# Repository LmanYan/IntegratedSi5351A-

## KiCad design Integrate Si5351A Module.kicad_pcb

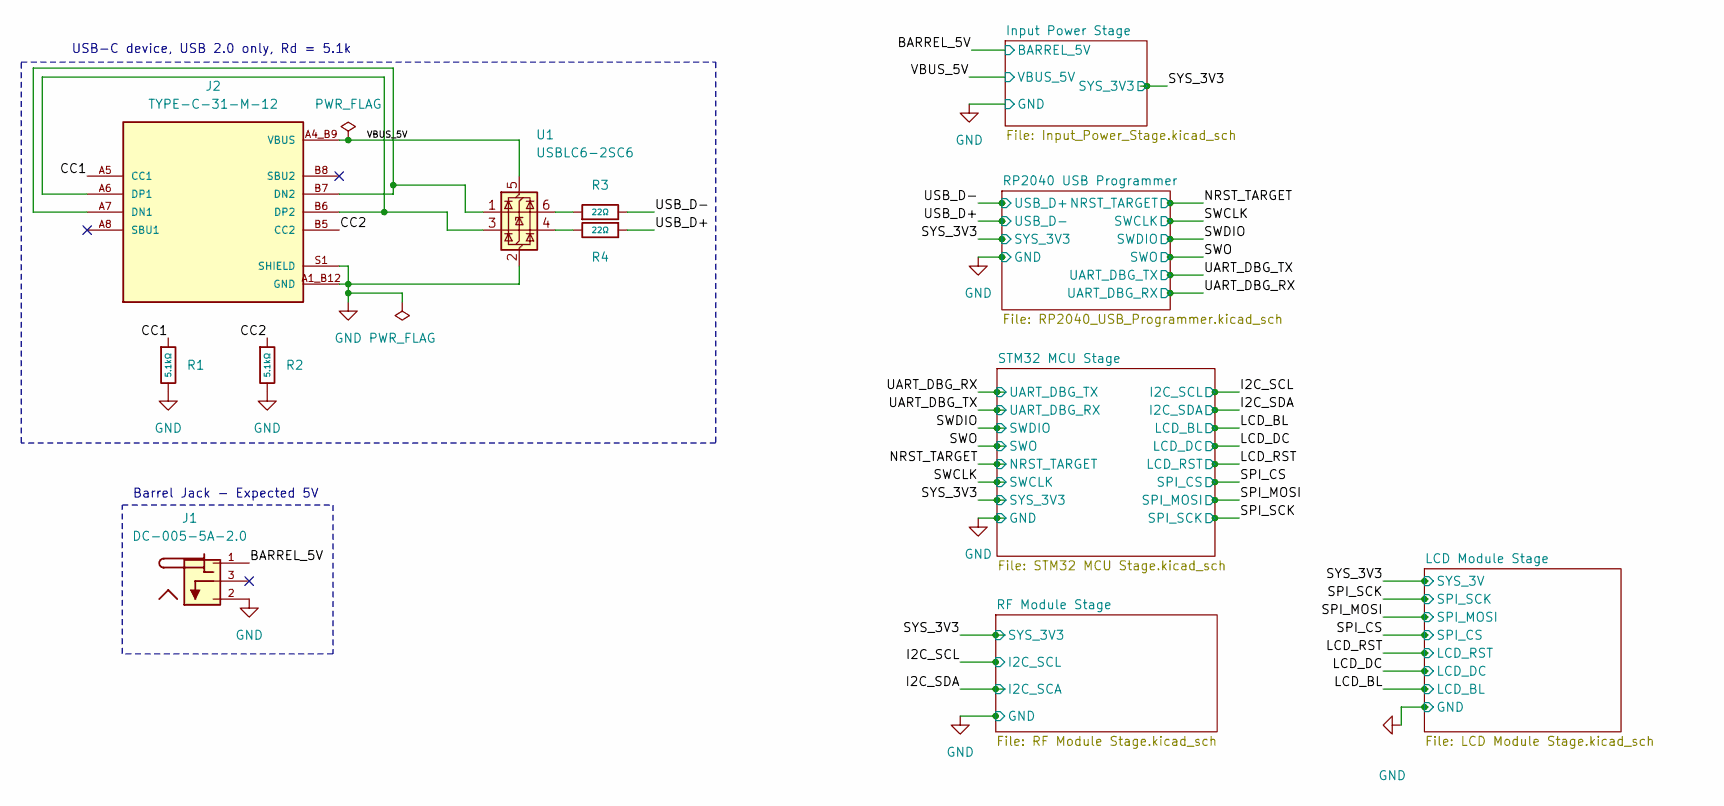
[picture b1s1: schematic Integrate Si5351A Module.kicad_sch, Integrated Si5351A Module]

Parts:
J1: DC-005-5A-2.0; XKB_DC-005-5A-2.0; PARTREV A0
J2: TYPE-C-31-M-12; HRO_TYPE-C-31-M-12; PARTREV 2020.12.08
R1, R2: 5.1kΩ; R_0603; Overload Voltage (Max) 75V; Tolerance ±1%; Part 0603WAF5101T5E; LCSC C23186
R3, R4: 22Ω; R_0603; Overload Voltage (Max) 75V; Tolerance ±1%; Part 0603WAF220JT5E; LCSC C23345
U1: USBLC6-2SC6; SOT-23-6

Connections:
/BARREL_5V: J1.1; also elsewhere on the board
/CC1: J2.A5 (CC1), R1.1
/CC2: J2.B5 (CC2), R2.1
/USB_D+: R4.1; also elsewhere on the board
/USB_D-: R3.2; also elsewhere on the board
GND: J1.2, J2.A1_B12 (GND), J2.B1_A12 (GND), J2.S1 (SHIELD), J2.S2 (SHIELD), J2.S3 (SHIELD), J2.S4 (SHIELD), R1.2, R2.2, U1.2 (GND); also elsewhere on the board
unnamed: J2.A7 (DN1), J2.B7 (DN2), U1.1 (I/O1)
unnamed: J2.A6 (DP1), J2.B6 (DP2), U1.3 (I/O2)
unnamed: R3.1, U1.6 (I/O1)
unnamed: R4.2, U1.4 (I/O2)
VBUS: J2.A4_B9 (VBUS), J2.B4_A9 (VBUS), U1.5 (VBUS); also elsewhere on the board

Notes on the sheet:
USB-C device, USB 2.0 only, Rd = 5.1k
Barrel Jack - Expected 5V

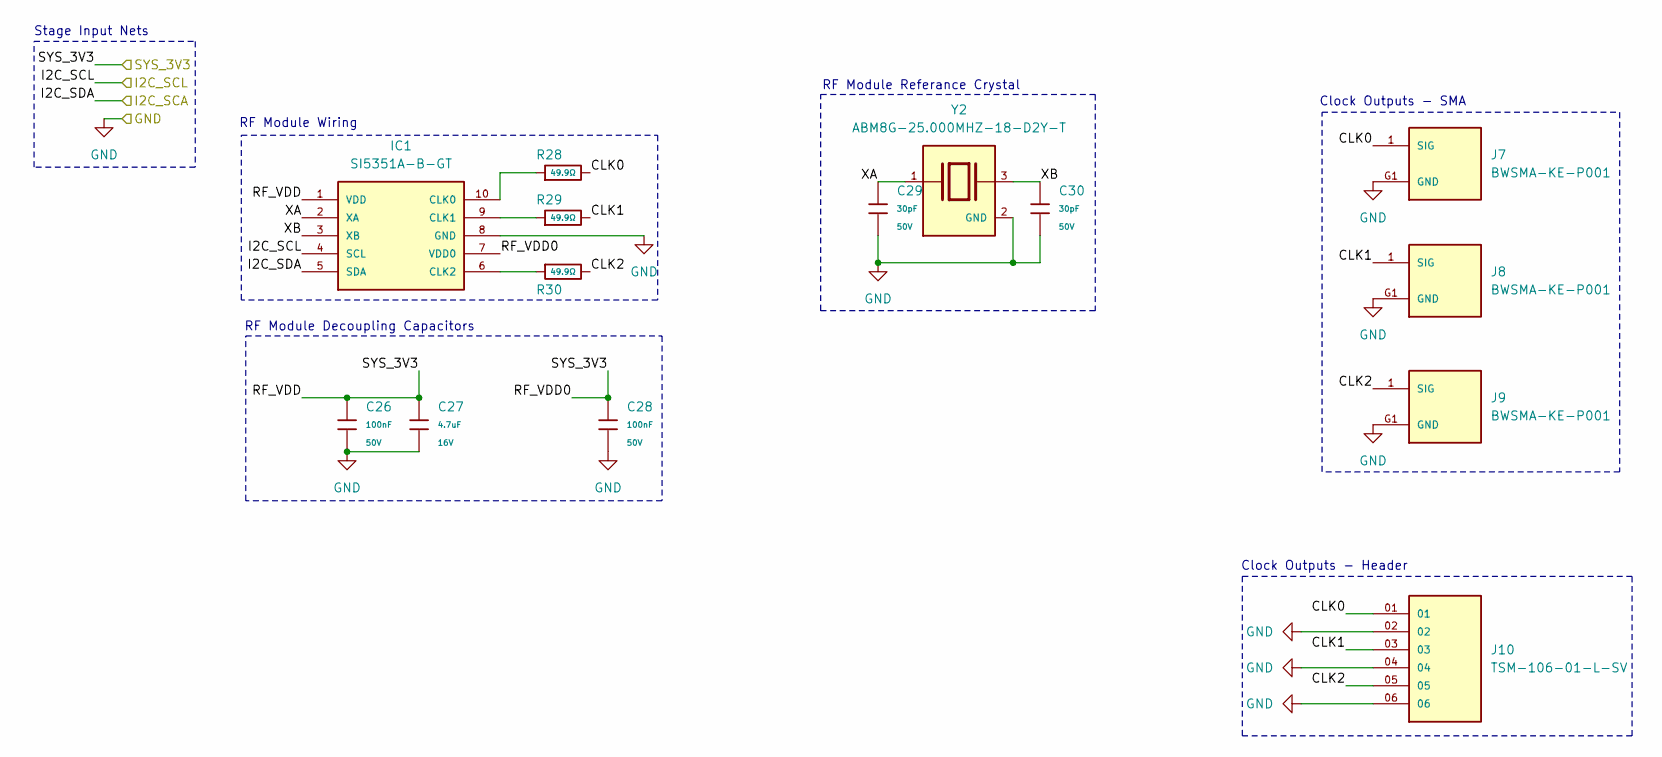
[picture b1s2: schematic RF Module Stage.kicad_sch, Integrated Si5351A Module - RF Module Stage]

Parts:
C26, C28: 100nF; C_0603; Voltage Rated 50V; Tolerance ±10%; Part CC0603KRX7R9BB104; LCSC C14663
C27: 4.7uF; C_0603; Voltage Rated 16V; Tolerance ±10%; Part CL10A475KO8NNNC; LCSC C19666
C29, C30: 30pF; C_0603; Voltage Rated 50V; Tolerance ±5%; Part 0603CG300J500NT; LCSC C1658
IC1: SI5351A-B-GT; SOP50P490X110-10N; MOUSER_PART_NUMBER 634-SI5351A-B-GT
J7, J8, J9: BWSMA-KE-P001; BATWIRELESS_BWSMA-KE-P001; PARTREV A
J10: TSM-106-01-L-SV; SAMTEC_TSM-106-01-L-SV
R28, R29, R30: 49.9Ω; R_0603; Overload Voltage (Max) 75V; Tolerance ±1%; Part 0603WAF499JT5E; LCSC C23185
Y2: ABM8G-25.000MHZ-18-D2Y-T; XTAL_ABM8G-25.000MHZ-18-D2Y-T; PARTREV 08.13.15

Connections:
/I2C_SCL: IC1.4 (SCL); also elsewhere on the board
/I2C_SDA: IC1.5 (SDA); also elsewhere on the board
/RF Module Stage/CLK0: J7.1 (SIG), J10.01, R28.2
/RF Module Stage/CLK1: J8.1 (SIG), J10.03, R29.2
/RF Module Stage/CLK2: J9.1 (SIG), J10.05, R30.2
/RF Module Stage/XA: C29.1, IC1.2 (XA), Y2.1
/RF Module Stage/XB: C30.1, IC1.3 (XB), Y2.3
/SYS_3V3: C26.1, C27.1, C28.1, IC1.1 (VDD), IC1.7 (VDD0); also elsewhere on the board
GND: C26.2, C27.2, C28.2, C29.2, C30.2, IC1.8 (GND), J7.G1 (GND), J7.G2 (GND), J7.G3 (GND), J7.G4 (GND), J8.G1 (GND), J8.G2 (GND), J8.G3 (GND), J8.G4 (GND), J9.G1 (GND), J9.G2 (GND), J9.G3 (GND), J9.G4 (GND), J10.02, J10.04, J10.06, Y2.2 (GND), Y2.4 (GND); also elsewhere on the board
unnamed: IC1.10 (CLK0), R28.1
unnamed: IC1.9 (CLK1), R29.1
unnamed: IC1.6 (CLK2), R30.1

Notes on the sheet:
RF Module Referance Crystal
RF Module Decoupling Capacitors
Clock Outputs - Header
RF Module Wiring
Stage Input Nets
Clock Outputs - SMA

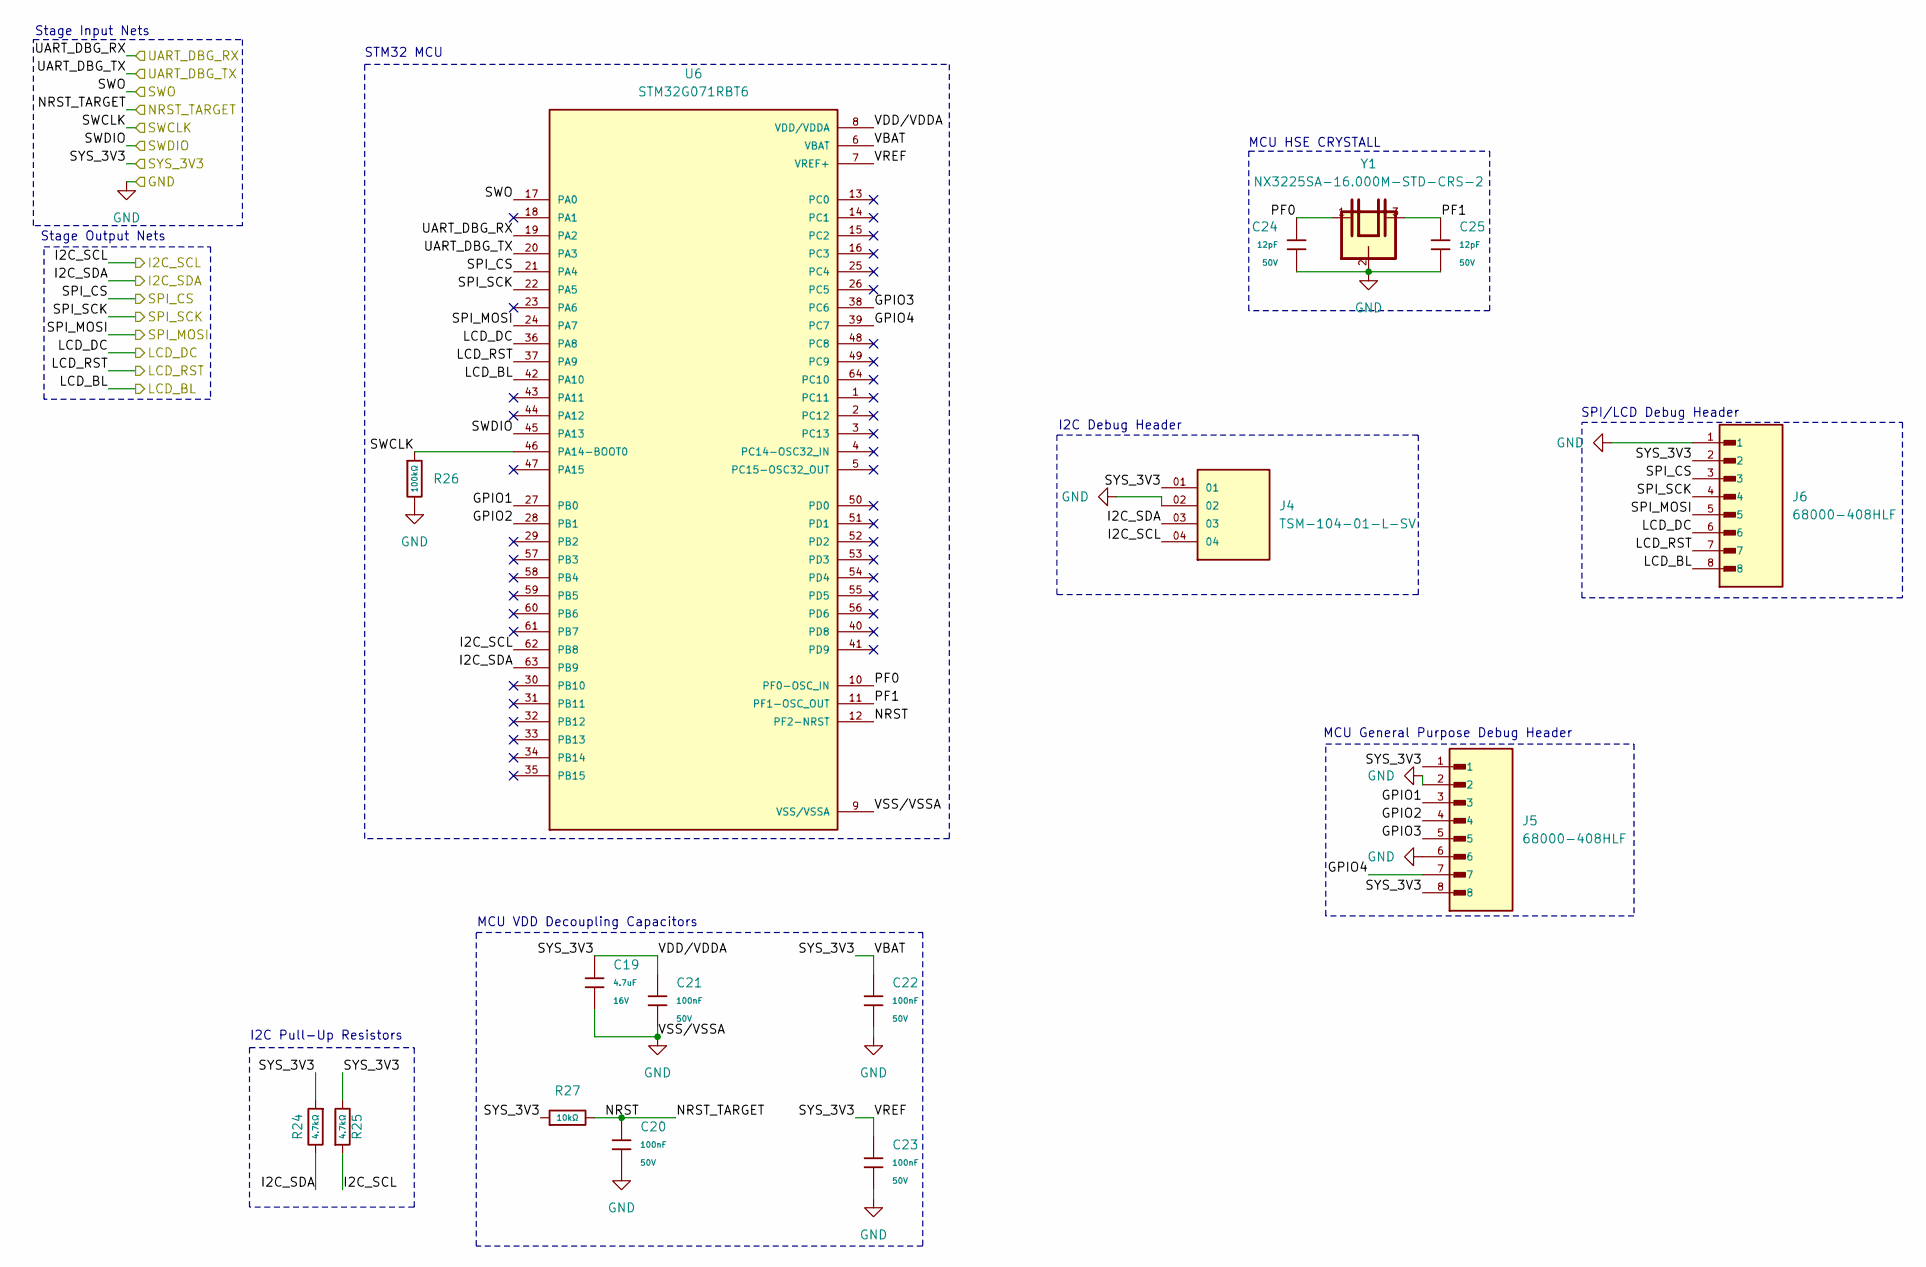
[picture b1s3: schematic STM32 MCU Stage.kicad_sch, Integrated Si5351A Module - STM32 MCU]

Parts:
C19: 4.7uF; C_0603; Voltage Rated 16V; Tolerance ±10%; Part CL10A475KO8NNNC; LCSC C19666
C20, C21, C22, C23: 100nF; C_0603; Voltage Rated 50V; Tolerance ±10%; Part CC0603KRX7R9BB104; LCSC C14663
C24, C25: 12pF; C_0603; Voltage Rated 50V; Tolerance ±5%; Part CL10C120JB8NNNC; LCSC C38523
J4: TSM-104-01-L-SV; SAMTEC_TSM-104-01-L-SV
J5, J6: 68000-408HLF; AMPHENOL_68000-408HLF; PARTREV DG
R24, R25: 4.7kΩ; R_0603; Overload Voltage (Max) 75V; Tolerance ±1%; Part 0603WAF4701T5E; LCSC C23162
R26: 100kΩ; R_0603; Overload Voltage (Max) 75V; Tolerance ±1%; Part 0603WAF1003T5E; LCSC C25803
R27: 10kΩ; R_0603; Overload Voltage (Max) 75V; Tolerance ±1%; Part 0603WAF1002T5E; LCSC C25804
U6: STM32G071RBT6; QFP50P1200X1200X160-64N; PARTREV 2
Y1: NX3225SA-16.000M-STD-CRS-2; OSCCC320X250X60N

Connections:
/I2C_SCL: J4.04, R25.1, U6.62 (PB8); also elsewhere on the board
/I2C_SDA: J4.03, R24.2, U6.63 (PB9); also elsewhere on the board
/LCD_BL: J6.8, U6.42 (PA10); also elsewhere on the board
/LCD_DC: J6.6, U6.36 (PA8); also elsewhere on the board
/LCD_RST: J6.7, U6.37 (PA9); also elsewhere on the board
/NRST_TARGET: C20.1, R27.2, U6.12 (PF2-NRST); also elsewhere on the board
/SPI_CS: J6.3, U6.21 (PA4); also elsewhere on the board
/SPI_MOSI: J6.5, U6.24 (PA7); also elsewhere on the board
/SPI_SCK: J6.4, U6.22 (PA5); also elsewhere on the board
/STM32 MCU Stage/GPIO1: J5.3, U6.27 (PB0)
/STM32 MCU Stage/GPIO2: J5.4, U6.28 (PB1)
/STM32 MCU Stage/GPIO3: J5.5, U6.38 (PC6)
/STM32 MCU Stage/GPIO4: J5.7, U6.39 (PC7)
/STM32 MCU Stage/PF0: C24.1, U6.10 (PF0-OSC_IN), Y1.1
/STM32 MCU Stage/PF1: C25.1, U6.11 (PF1-OSC_OUT), Y1.3
/SWCLK: R26.1, U6.46 (PA14-BOOT0); also elsewhere on the board
/SWDIO: U6.45 (PA13); also elsewhere on the board
/SWO: U6.17 (PA0); also elsewhere on the board
/SYS_3V3: C19.1, C21.1, C22.1, C23.1, J4.01, J5.1, J5.8, J6.2, R24.1, R25.2, R27.1, U6.6 (VBAT), U6.7 (VREF+), U6.8 (VDD/VDDA); also elsewhere on the board
/UART_DBG_RX: U6.20 (PA3); also elsewhere on the board
/UART_DBG_TX: U6.19 (PA2); also elsewhere on the board
GND: C19.2, C20.2, C21.2, C22.2, C23.2, C24.2, C25.2, J4.02, J5.2, J5.6, J6.1, R26.2, U6.9 (VSS/VSSA), Y1.2, Y1.4; also elsewhere on the board

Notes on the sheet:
STM32 MCU
SPI/LCD Debug Header
Stage Input Nets
I2C Pull-Up Resistors
MCU General Purpose Debug Header
MCU VDD Decoupling Capacitors
Stage Output Nets
I2C Debug Header
MCU HSE CRYSTALL

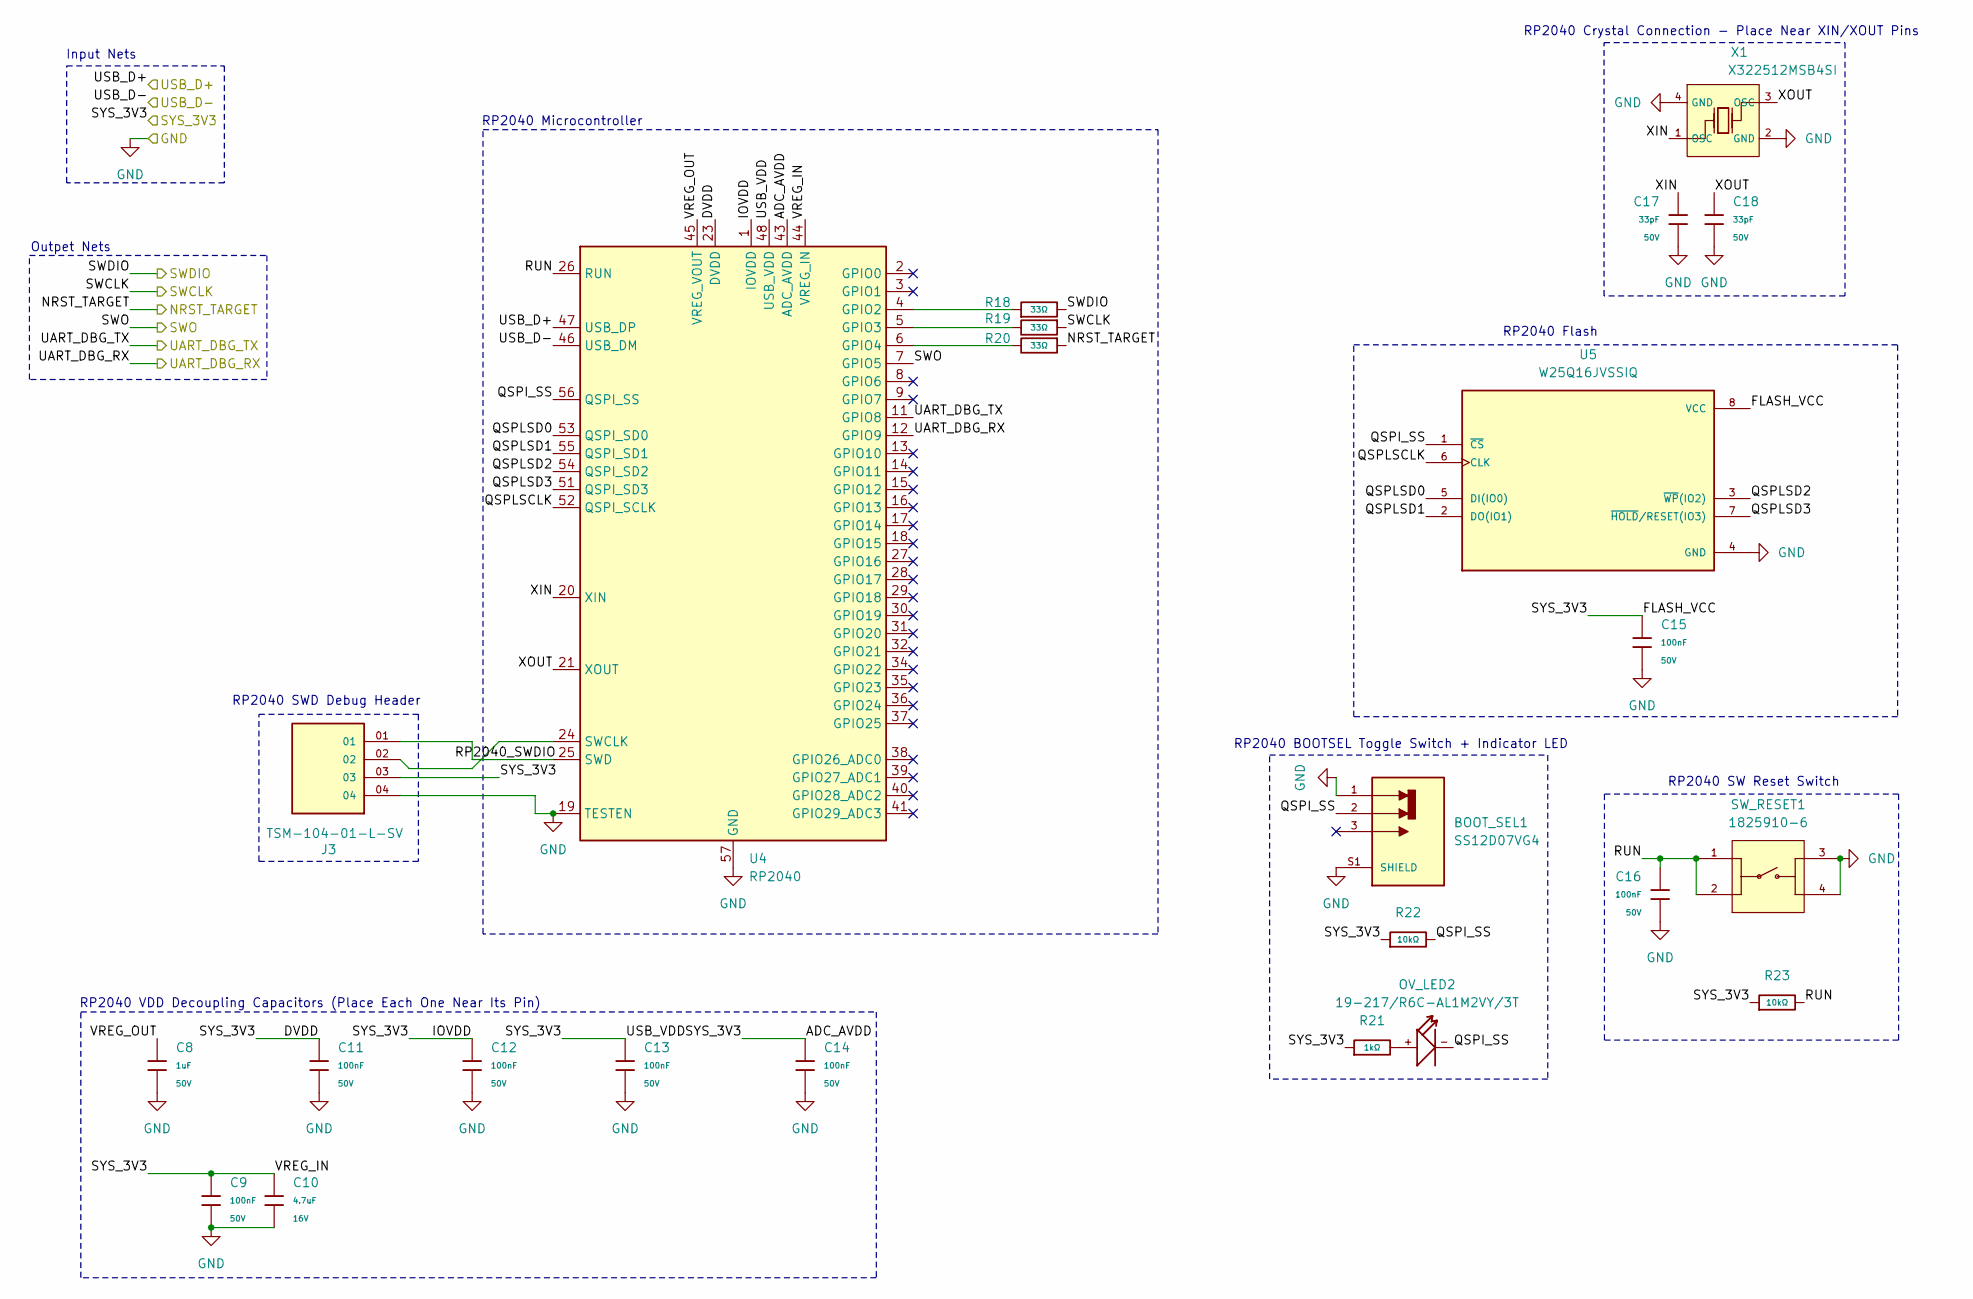
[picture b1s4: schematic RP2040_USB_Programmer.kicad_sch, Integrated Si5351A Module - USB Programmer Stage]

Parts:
BOOT_SEL1: SS12D07VG4; SW_SS12D07VG4; PARTREV 1
C8: 1uF; C_0603; Voltage Rated 50V; Tolerance ±10%; Part CL10A105KB8NNNC; LCSC C15849
C9, C11, C12, C13, C14, C15, C16: 100nF; C_0603; Voltage Rated 50V; Tolerance ±10%; Part CC0603KRX7R9BB104; LCSC C14663
C10: 4.7uF; C_0603; Voltage Rated 16V; Tolerance ±10%; Part CL10A475KO8NNNC; LCSC C19666
C17, C18: 33pF; C_0603; Voltage Rated 50V; Tolerance ±5%; Part CL10C330JB8NNNC; LCSC C1663
J3: TSM-104-01-L-SV; SAMTEC_TSM-104-01-L-SV
OV_LED2: 19-217/R6C-AL1M2VY/3T; LED-0603; MPN 19-217-R6C-AL1M2VY-3T
R18, R19, R20: 33Ω; R_0603; Overload Voltage (Max) 75V; Tolerance ±1%; Part 0603WAF330JT5E; LCSC C23140
R21: 1kΩ; R_0603; Overload Voltage (Max) 75V; Tolerance ±1%; Part 0603WAF1001T5E; LCSC C21190
R22, R23: 10kΩ; R_0603; Overload Voltage (Max) 75V; Tolerance ±1%; Part 0603WAF1002T5E; LCSC C25804
SW_RESET1: 1825910-6; SW_1825910-6-4; PARTREV C10
U4: RP2040; QFN-56-1EP_7x7mm_P0.4mm_EP3.2x3.2mm_ThermalVias; LCSC C2040
U5: W25Q16JVSSIQ; SOIC127P790X216-8N
X1: X322512MSB4SI; CRYSTAL-SMD_4P-L3.2-W2.5-BL; Frequency Tolerance ±10ppm; Part X322512MSB4SI; LCSC C9002

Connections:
/NRST_TARGET: R20.1; also elsewhere on the board
/RP2040 USB Programmer/QSPI_SS: BOOT_SEL1.2, OV_LED2.-, R22.2, U4.56 (QSPI_SS), U5.1 (~CS)
/RP2040 USB Programmer/QSPLSCLK: U4.52 (QSPI_SCLK), U5.6 (CLK)
/RP2040 USB Programmer/QSPLSD0: U4.53 (QSPI_SD0), U5.5 (DI(IO0))
/RP2040 USB Programmer/QSPLSD1: U4.55 (QSPI_SD1), U5.2 (DO(IO1))
/RP2040 USB Programmer/QSPLSD2: U4.54 (QSPI_SD2), U5.3 (~WP(IO2))
/RP2040 USB Programmer/QSPLSD3: U4.51 (QSPI_SD3), U5.7 (~HOLD/RESET(IO3))
/RP2040 USB Programmer/RUN: C16.2, R23.2, SW_RESET1.1, SW_RESET1.2, U4.26 (RUN)
/RP2040 USB Programmer/VREG_OUT: C8.2, U4.45 (VREG_VOUT)
/RP2040 USB Programmer/XIN: C17.1, U4.20 (XIN), X1.1 (OSC)
/RP2040 USB Programmer/XOUT: C18.1, U4.21 (XOUT), X1.3 (OSC)
/SWCLK: R19.1; also elsewhere on the board
/SWDIO: R18.2; also elsewhere on the board
/SWO: U4.7 (GPIO5); also elsewhere on the board
/SYS_3V3: C9.2, C10.1, C11.2, C12.2, C13.1, C14.2, C15.2, J3.03, R21.1, R22.1, R23.1, U4.1 (IOVDD), U4.10 (IOVDD), U4.22 (IOVDD), U4.23 (DVDD), U4.33 (IOVDD), U4.42 (IOVDD), U4.43 (ADC_AVDD), U4.44 (VREG_IN), U4.48 (USB_VDD), U4.49 (IOVDD), U4.50 (DVDD), U5.8 (VCC); also elsewhere on the board
/UART_DBG_RX: U4.12 (GPIO9); also elsewhere on the board
/UART_DBG_TX: U4.11 (GPIO8); also elsewhere on the board
/USB_D+: U4.46 (USB_DM); also elsewhere on the board
/USB_D-: U4.47 (USB_DP); also elsewhere on the board
GND: BOOT_SEL1.1, BOOT_SEL1.S1 (SHIELD), BOOT_SEL1.S2 (SHIELD), C8.1, C9.1, C10.2, C11.1, C12.1, C13.2, C14.1, C15.1, C16.1, C17.2, C18.2, J3.04, SW_RESET1.3, SW_RESET1.4, U4.19 (TESTEN), U4.57 (GND), U5.4 (GND), X1.2 (GND), X1.4 (GND); also elsewhere on the board
unnamed: OV_LED2.+, R21.2
unnamed: R18.1, U4.4 (GPIO2)
unnamed: R19.2, U4.5 (GPIO3)
unnamed: R20.2, U4.6 (GPIO4)
unnamed: J3.02, U4.24 (SWCLK)
unnamed: J3.01, U4.25 (SWD)

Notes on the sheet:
Outpet Nets
RP2040 SWD Debug Header
RP2040 Microcontroller
Input Nets
RP2040 Crystal Connection - Place Near XIN/XOUT Pins
RP2040 BOOTSEL Toggle Switch + Indicator LED
RP2040 SW Reset Switch
RP2040 Flash
RP2040 VDD Decoupling Capacitors (Place Each One Near Its Pin)

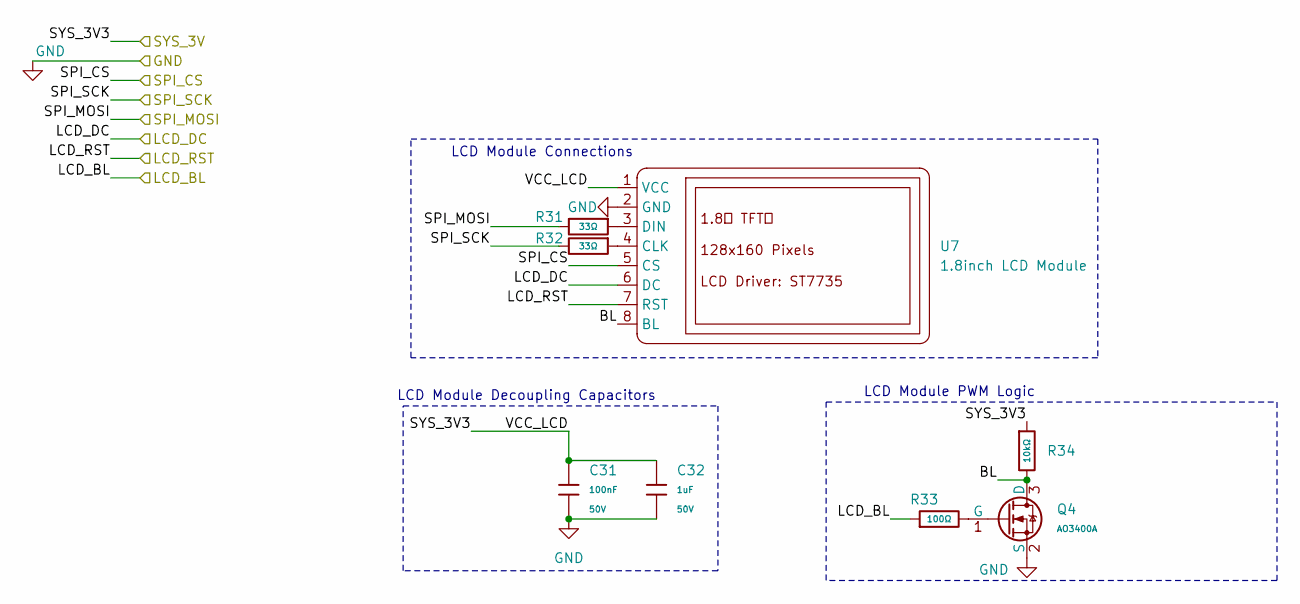
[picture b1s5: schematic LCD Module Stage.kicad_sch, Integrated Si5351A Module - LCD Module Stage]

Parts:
C31: 100nF; C_0603; Voltage Rated 50V; Tolerance ±10%; Part CC0603KRX7R9BB104; LCSC C14663
C32: 1uF; C_0603; Voltage Rated 50V; Tolerance ±10%; Part CL10A105KB8NNNC; LCSC C15849
Q4: AO3400A; Q_SOT-23; Part AO3400A; LCSC C20917
R31, R32: 33Ω; R_0603; Overload Voltage (Max) 75V; Tolerance ±1%; Part 0603WAF330JT5E; LCSC C23140
R33: 100Ω; R_0603; Overload Voltage (Max) 75V; Tolerance ±1%; Part 0603WAF1000T5E; LCSC C22775
R34: 10kΩ; R_0603; Overload Voltage (Max) 75V; Tolerance ±1%; Part 0603WAF1002T5E; LCSC C25804
U7: 1.8inch LCD Module; Waveshare 1.8inch LCD Module

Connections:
/LCD Module Stage/BL: Q4.3 (D), R34.2, U7.8 (BL)
/LCD_BL: R33.1; also elsewhere on the board
/LCD_DC: U7.6 (DC); also elsewhere on the board
/LCD_RST: U7.7 (RST); also elsewhere on the board
/SPI_CS: U7.5 (CS); also elsewhere on the board
/SPI_MOSI: R31.2; also elsewhere on the board
/SPI_SCK: R32.2; also elsewhere on the board
/SYS_3V3: C31.1, C32.1, R34.1, U7.1 (VCC); also elsewhere on the board
GND: C31.2, C32.2, Q4.2 (S), U7.2 (GND); also elsewhere on the board
unnamed: Q4.1 (G), R33.2
unnamed: R32.1, U7.4 (CLK)
unnamed: R31.1, U7.3 (DIN)

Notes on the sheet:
LCD Module Decoupling Capacitors
LCD Module Connections
LCD Module PWM Logic

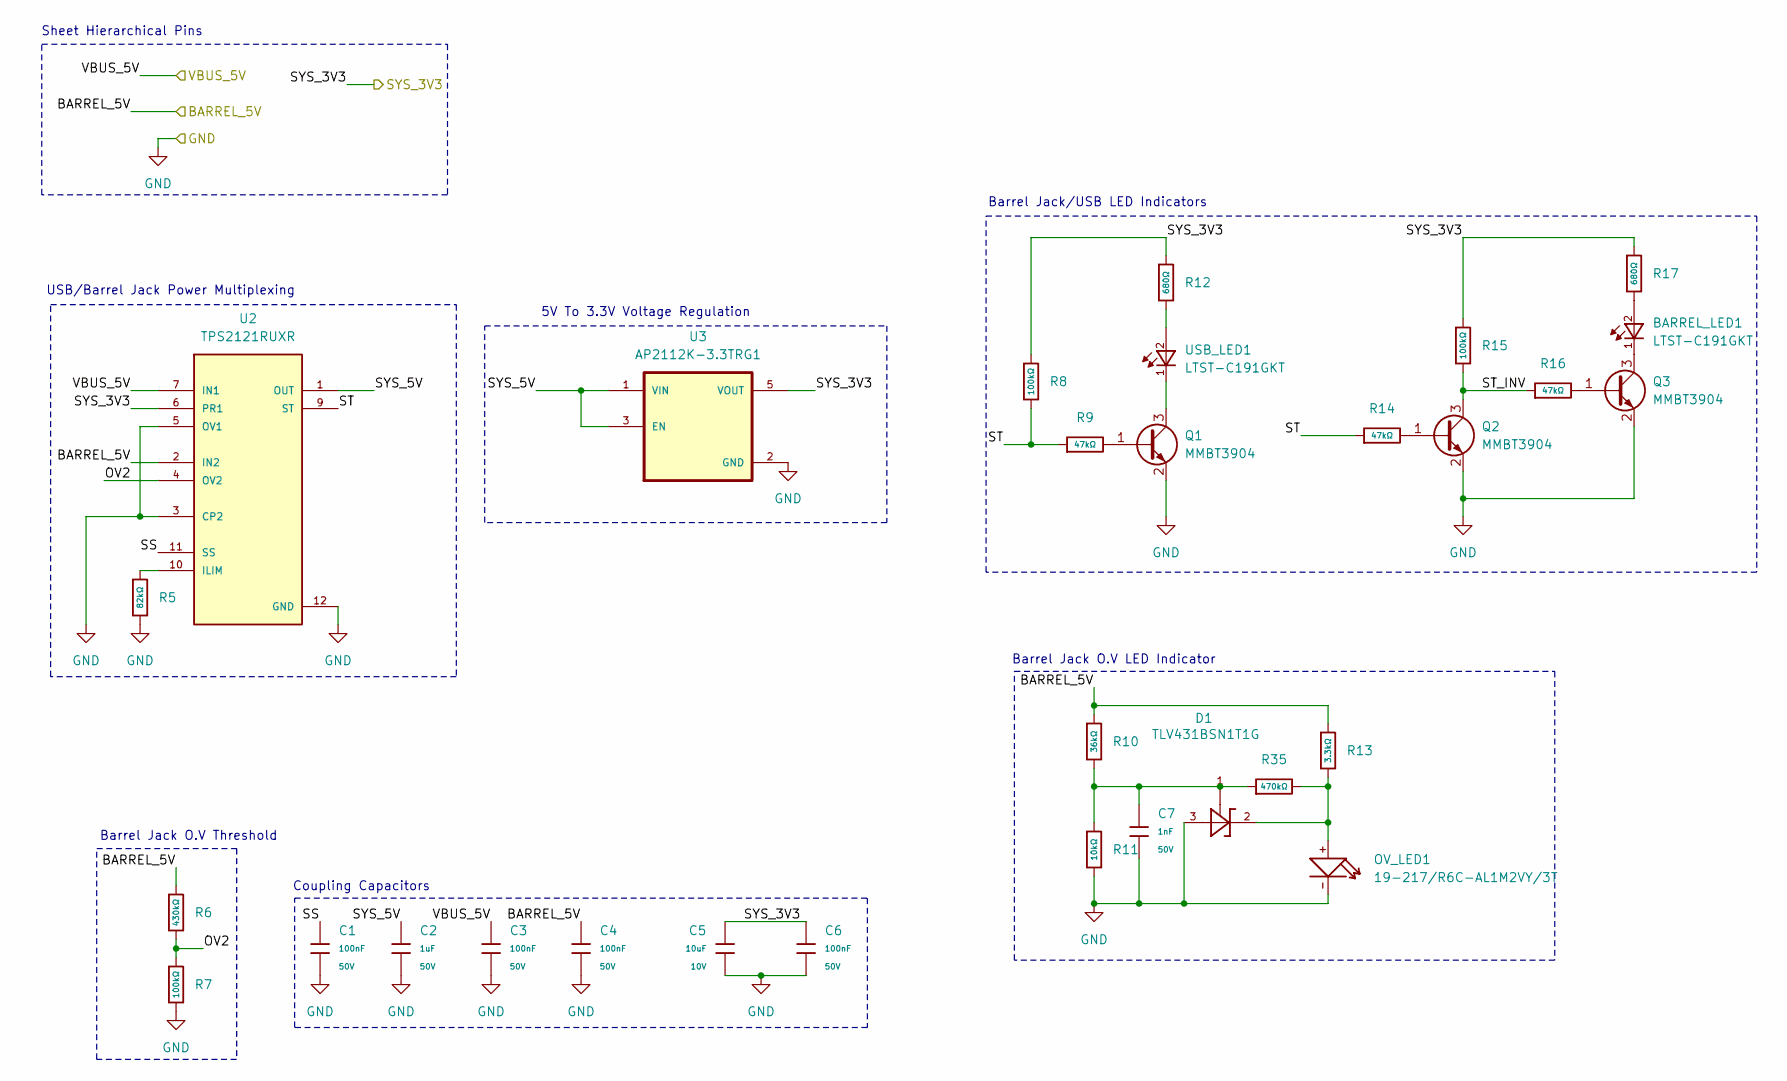
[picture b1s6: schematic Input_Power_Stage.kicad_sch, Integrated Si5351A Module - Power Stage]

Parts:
BARREL_LED1: LTST-C191GKT; 0603
C1, C3, C4, C6: 100nF; C_0603; Voltage Rated 50V; Tolerance ±10%; Part CC0603KRX7R9BB104; LCSC C14663
C2: 1uF; C_0603; Voltage Rated 50V; Tolerance ±10%; Part CL10A105KB8NNNC; LCSC C15849
C5: 10uF; C_0603; Voltage Rated 10V; Tolerance ±10%; Part CL10A106KP8NNNC; LCSC C19702
C7: 1nF; C_0603; Voltage Rated 50V; Tolerance ±10%; Part CL10B102KB8NNNC; LCSC C1588
D1: TLV431BSN1T1G; SOT23; MPN TLV431BSN1T1G /TLV431AFTA
OV_LED1: 19-217/R6C-AL1M2VY/3T; LED-0603; MPN 19-217-R6C-AL1M2VY-3T
Q1, Q2, Q3: MMBT3904; SOT-23
R5: 82kΩ; R_0603; Overload Voltage (Max) 75V; Tolerance ±1%; Part 0603WAF8202T5E; LCSC C23254
R6: 430kΩ; R_0603; Overload Voltage (Max) 75V; Tolerance ±1%; Part 0603WAF4303T5E; LCSC C25969
R7, R8, R15: 100kΩ; R_0603; Overload Voltage (Max) 75V; Tolerance ±1%; Part 0603WAF1003T5E; LCSC C25803
R9, R14, R16: 47kΩ; R_0603; Overload Voltage (Max) 75V; Tolerance ±1%; Part 0603WAF4702T5E; LCSC C25819
R10: 36kΩ; R_0603; Overload Voltage (Max) 75V; Tolerance ±1%; Part 0603WAF3602T5E; LCSC C23147
R11: 10kΩ; R_0603; Overload Voltage (Max) 75V; Tolerance ±1%; Part 0603WAF1002T5E; LCSC C25804
R12, R17: 680Ω; R_0603; Overload Voltage (Max) 75V; Tolerance ±1%; Part 0603WAF6800T5E; LCSC C23228
R13: 3.3kΩ; R_0603; Overload Voltage (Max) 75V; Tolerance ±1%; Part 0603WAF3301T5E; LCSC C22978
R35: 470kΩ; R_0603; Overload Voltage (Max) 75V; Tolerance ±1%; Part 0603WAF4703T5E; LCSC C23178
U2: TPS2121RUXR; IC_TPS2121RUXR
U3: AP2112K-3.3TRG1; SOT95P285X140-5N; PARTREV 2-2
USB_LED1: LTST-C191GKT; 0603

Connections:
/BARREL_5V: C4.1, R6.1, R10.1, R13.1, U2.2 (IN2), U2.2_1 (IN2); also elsewhere on the board
/Input Power Stage/OV2: R6.2, R7.1, U2.4 (OV2)
/Input Power Stage/SS: C1.1, U2.11 (SS)
/Input Power Stage/ST: R8.2, R9.1, R14.1, U2.9 (ST)
/Input Power Stage/ST_INV: Q2.3 (C), R15.2, R16.1
/Input Power Stage/SYS_5V: C2.1, U2.1 (OUT), U2.1_1 (OUT), U2.8 (OUT), U2.8_1 (OUT), U3.1 (VIN), U3.3 (EN)
/SYS_3V3: C5.1, C6.2, R8.1, R12.1, R15.1, R17.1, U2.6 (PR1), U3.5 (VOUT); also elsewhere on the board
GND: C1.2, C2.2, C3.2, C4.2, C5.2, C6.1, C7.2, D1.3, OV_LED1.-, Q1.2 (E), Q2.2 (E), Q3.2 (E), R5.2, R7.2, R11.2, U2.3 (CP2), U2.5 (OV1), U2.12 (GND), U3.2 (GND); also elsewhere on the board
unnamed: BARREL_LED1.2, R17.2
unnamed: C7.1, D1.1, R10.2, R11.1, R35.1
unnamed: D1.2, OV_LED1.+, R13.2, R35.2
unnamed: Q1.1 (B), R9.2
unnamed: Q1.3 (C), USB_LED1.1
unnamed: Q2.1 (B), R14.2
unnamed: Q3.1 (B), R16.2
unnamed: BARREL_LED1.1, Q3.3 (C)
unnamed: R12.2, USB_LED1.2
unnamed: R5.1, U2.10 (ILIM)
VBUS: C3.1, U2.7 (IN1), U2.7_1 (IN1); also elsewhere on the board

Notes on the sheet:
5V To 3.3V Voltage Regulation
USB/Barrel Jack Power Multiplexing
Sheet Hierarchical Pins
Barrel Jack O.V Threshold
Coupling Capacitors
Barrel Jack/USB LED Indicators
Barrel Jack O.V LED Indicator

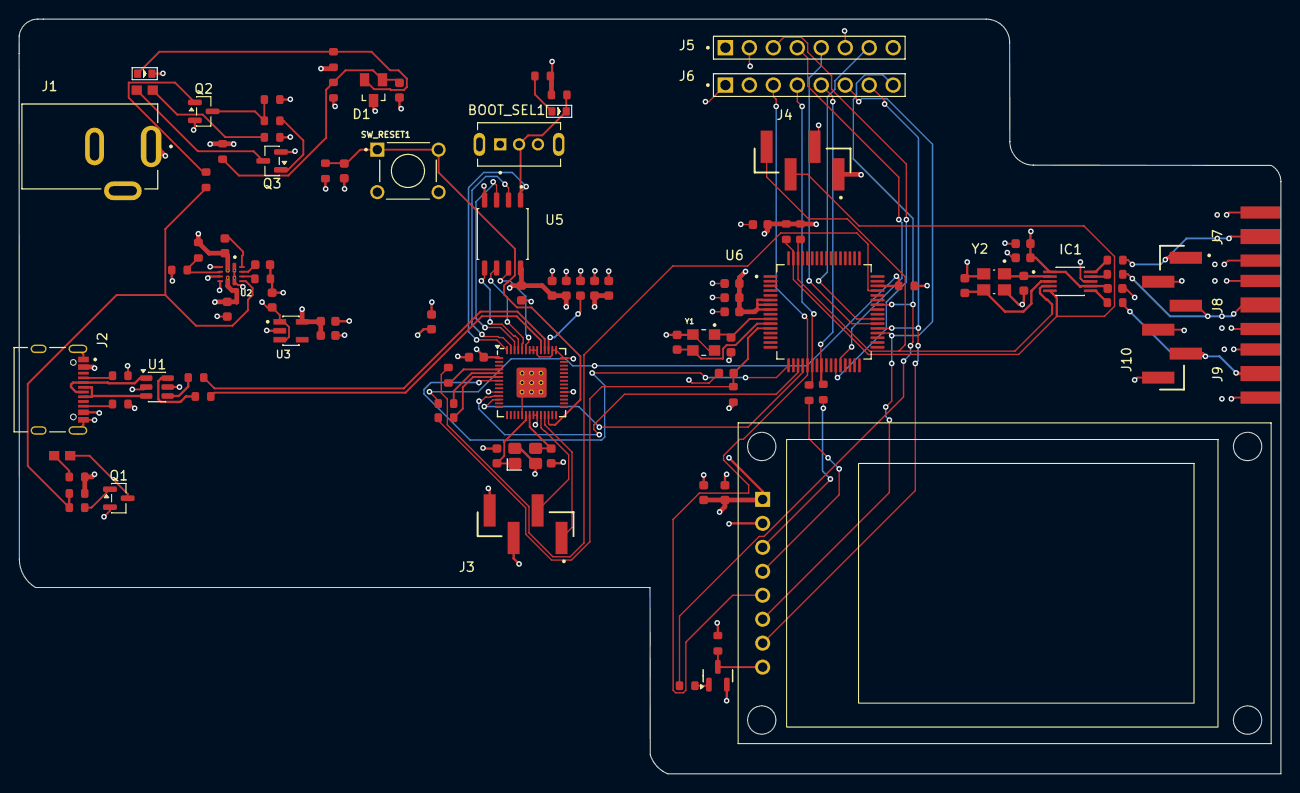
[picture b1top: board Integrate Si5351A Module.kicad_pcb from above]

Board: 4 copper layers, 133.7 x 80.0 mm, 98 parts (0 on the bottom side), 75 nets.

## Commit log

2026-02-09 Initial files
2026-02-09 Added Footprints folder
2026-02-09 - Renamed USB-C connector folder - Finished USB-C connector schematic
2026-02-10 Finished 5V_Barrel over voltage red LED indicator
2026-02-10 Finished Power Stage
2026-02-10 Organized Input_Power_Stage.kicad_sch
2026-02-12 Finished USB programming stage
2026-02-13 Finished STM32 Stage
2026-02-13 Fixed path and sheet name
2026-02-13 RF Module Stage Schematic Complete
2026-02-14 LCD Stage Finished
2026-03-17 - Added Hysteresis resistor on TLV431BSN1T1G - Lowered TLV431BSN1T1G impedance values for resistors on the voltage divider
2026-03-17 - Added reverse polarity protection for barrel jack
2026-03-17 - Added TVS ESD Protection diode on J1
2026-03-17 Changed values of R3 and R4 to comply with USB RP guidelines
2026-03-17 -Added bouncing prevention capacitor on BOOT_SEL
